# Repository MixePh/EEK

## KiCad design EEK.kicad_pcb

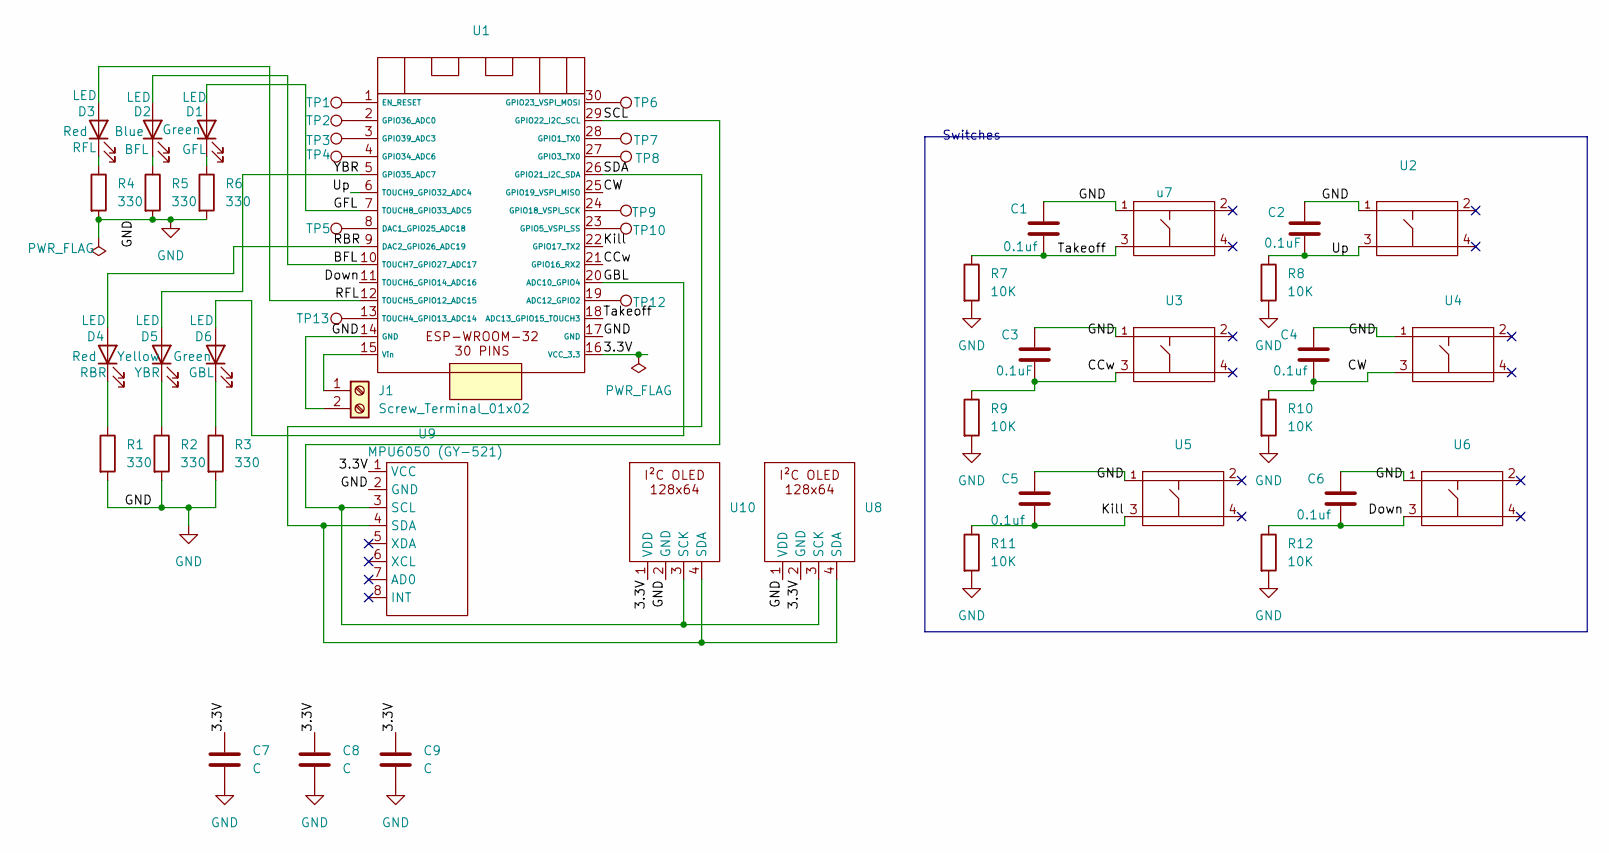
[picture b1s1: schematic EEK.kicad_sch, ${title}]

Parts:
C1, C4, C5, C6: 0.1uf; C_Disc_D8.0mm_W2.5mm_P5.00mm
C2, C3: 0.1uF; C_Disc_D8.0mm_W2.5mm_P5.00mm
C7, C8, C9: C; C_Radial_D10.0mm_H12.5mm_P5.00mm
D1, D2, D3, D4, D5, D6: LED; LED_D5.0mm
J1: Screw_Terminal_01x02; TerminalBlock_Phoenix_MKDS-1,5-2_1x02_P5.00mm_Horizontal
R1, R2, R3, R4, R5, R6: 330; R_Axial_DIN0207_L6.3mm_D2.5mm_P10.16mm_Horizontal
R7, R8, R9, R10, R11, R12: 10K; R_Axial_DIN0207_L6.3mm_D2.5mm_P10.16mm_Horizontal
TP1, TP2, TP3, TP4, TP5, TP6, TP7, TP8, TP9, TP10, TP12, TP13: TestPoint; TestPoint_Plated_Hole_D2.0mm
U1: ESP-WROOM_32
U2, U3, U4, U5, U6: SW_Tactile
U8, U10: PinHeader_1x04_P2.54mm_Vertical
U9: PinHeader_1x08_P2.54mm_Vertical
u7: SW_Tactile

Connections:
/3.3V: C7.1, C8.1, C9.1, U1.16 (VCC_3.3), U8.2 (GND), U9.1 (VCC), U10.1 (VDD)
/BFL: D2.2 (A), U1.10 (TOUCH7_GPIO27_ADC17)
/CCw: C3.2, R9.1, U1.21 (GPIO16_RX2), U3.3
/CW: C4.2, R10.1, U1.25 (GPIO19_VSPI_MISO), U4.3
/Down: C6.2, R12.1, U1.11 (TOUCH6_GPIO14_ADC16), U6.3
/GBL: D6.2 (A), U1.20 (ADC10_GPIO4)
/GFL: D1.2 (A), U1.7 (TOUCH8_GPIO33_ADC5)
/Kill: C5.2, R11.1, U1.22 (GPIO17_TX2), U5.3
/RBR: D4.2 (A), U1.9 (DAC2_GPIO26_ADC19)
/RFL: D3.2 (A), U1.12 (TOUCH5_GPIO12_ADC15)
/SCL: U1.29 (GPIO22_I2C_SCL), U8.3 (SCK), U9.3 (SCL), U10.3 (SCK)
/SDA: U1.26 (GPIO21_I2C_SDA), U8.4 (SDA), U9.4 (SDA), U10.4 (SDA)
/Takeoff: C1.2, R7.1, U1.18 (ADC13_GPIO15_TOUCH3), u7.3
/Up: C2.2, R8.1, U1.6 (TOUCH9_GPIO32_ADC4), U2.3
/YBR: D5.2 (A), U1.5 (GPIO35_ADC7)
GND: C1.1, C2.1, C3.1, C4.1, C5.1, C6.1, C7.2, C8.2, C9.2, J1.2, R1.2, R2.2, R3.2, R4.2, R5.2, R6.2, R7.2, R8.2, R9.2, R10.2, R11.2, R12.2, U1.14 (GND), U1.17 (GND), U2.1, U3.1, U4.1, U5.1, U6.1, U8.1 (VDD), U9.2 (GND), U10.2 (GND), u7.1
unnamed: D1.1 (K), R6.1
unnamed: D2.1 (K), R5.1
unnamed: D3.1 (K), R4.1
unnamed: D4.1 (K), R1.1
unnamed: D5.1 (K), R2.1
unnamed: D6.1 (K), R3.1
unnamed: J1.1, U1.15 (Vin)
unnamed: TP12.1, U1.19 (ADC12_GPIO2)
unnamed: TP5.1, U1.8 (DAC1_GPIO25_ADC18)
unnamed: TP1.1, U1.1 (EN_RESET)
unnamed: TP7.1, U1.28 (GPIO1_TX0)
unnamed: TP8.1, U1.27 (GPIO3_TX0)
unnamed: TP10.1, U1.23 (GPIO5_VSPI_SS)
unnamed: TP9.1, U1.24 (GPIO18_VSPI_SCK)
unnamed: TP6.1, U1.30 (GPIO23_VSPI_MOSI)
unnamed: TP4.1, U1.4 (GPIO34_ADC6)
unnamed: TP2.1, U1.2 (GPIO36_ADC0)
unnamed: TP3.1, U1.3 (GPIO39_ADC3)
unnamed: TP13.1, U1.13 (TOUCH4_GPIO13_ADC14)

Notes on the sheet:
Switches

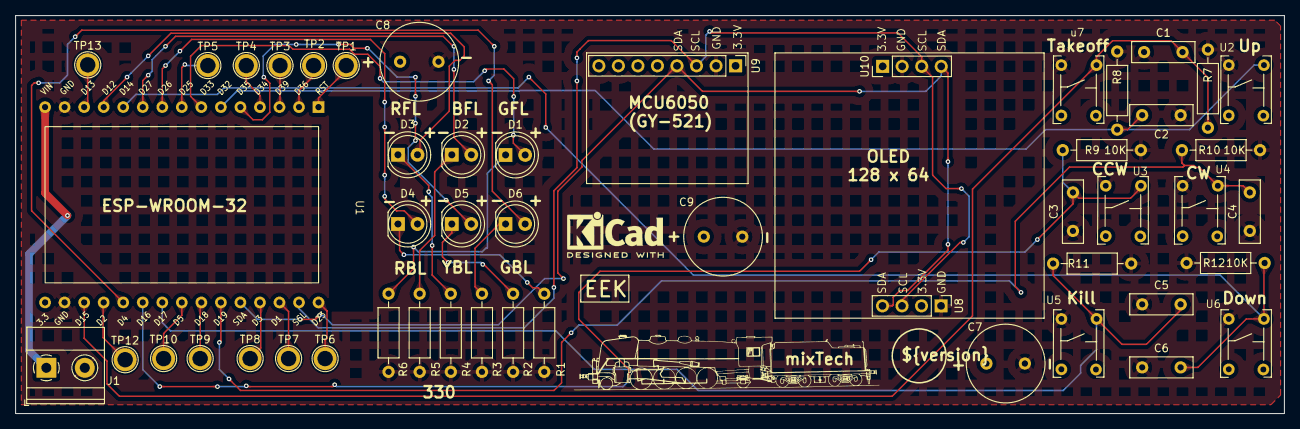
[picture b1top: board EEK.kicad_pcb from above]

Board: 2 copper layers, 165.0 x 51.8 mm, 52 parts (1 on the bottom side), 35 nets.

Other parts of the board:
G001: LOGO; LOGO mixTech
QR1: githubEEK

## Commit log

2024-03-11 V1.0 EEK
    original version Kicad 8 EEK for EEK TechExloration course
2024-03-11 update
    update for production
2024-03-11 Updat silkscreen
    REf U1 move
2024-03-11 Update . gitignore to exclude gerber files
2024-03-11 Update .gitignore
    change directory name old gerbers
2024-03-12 add 3D switches
    add switches in the 3D view
2024-03-12 add PCB features
    Add PCB deatures un PCB Editor
2024-03-12 update .gitignore
    update ..gitignore
2024-03-15 fix the bug on OLED power supply pin1 and 2 inverted (3.3V and GND)
    Fix the bug on the OLED power supply pins which have been inverted PIN 1 3.3V and pin 2 GND
2024-03-15 update version number V1.1
    update version number to 1.1
2024-03-15 fix bug with version number on pcb ${version}
    fix bug with version number on pcb ${version}
2024-03-15 change the footprint of the tactil switch which was not correct
    Change the footprint of the tactil switch which was not correct
2024-03-15 Change the direction of the MCU6050 connector
    Change the direction of the MCU6050 connector pin 1 to pin 8
2024-03-15 add project name EEK on the silkscreen layer
    Add project name "EEK" on the silkscreen layer
2024-03-19 Add 141R mixTech logo
    Add 141R mixTech logo
2024-03-19 Add exclusion zone for the antenna of the ESP32
    Add exclusion zone for the antenna of the ESP32
2024-03-20 Addvcapacitors for the switches and connector for battery
    Add capacitors for the switches and connector for battery Vin
2024-03-21 add footprint for oled with gnd on pin 1, improve the copper field
    Add a second footprint for oled with the gnd on pin 1 instead pin 2. Improve the copper filed
2024-03-22 improve silkscreen, add capacitors on 3.3V, improve copper filed
    improve silkscreen, add capacitors on 3.3V, improve copper filed
2024-03-23 copper filed and silkscreen improvement
    copper filed and silkscreen improvement
2024-03-24 add pull down 10K resistors on the switche
    add pull down 10K resistors on the switche
2024-03-25 Invert LED D1 and LED D3
    Invert LED D1 and LED D3
2024-03-25 Version SMD before introduce SMD foot print
2024-03-25 Change footprint to SMD
    Change footprint to SMD
2024-03-26 Invert Takeoff and Up switches
    Invert Takeoff and Up switches
2024-03-31 improve the silkscreen
    improve the silkscreen
2024-04-13 add bom
    add bom plugin
2024-04-15 gerber files V1.1 and QR code on silkscreen
    gerber files V1.1 and QR code on silkscreen
2024-04-30 update and developpement of accelerometers and gyroscopes
    update and developpement of accelerometers and gyroscopesfor MPU6050
2024-05-12 change yellow led connection from GPIO 25 to GPIO 35
    Change the connection of tellow led that is has an issue when the wifi is used
2024-08-29 add teardrops
    Add teardrops
2025-10-02 changement redresseur
    Passage d'un redresseur triphasé à un monophasé
